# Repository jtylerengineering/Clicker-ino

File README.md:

# Clicker-ino (WIP)
A simple(ish) 433 mhz RF transceiver that uses an Arduino Uno R3 and an LCD Shield to display morse code inputs as  English.

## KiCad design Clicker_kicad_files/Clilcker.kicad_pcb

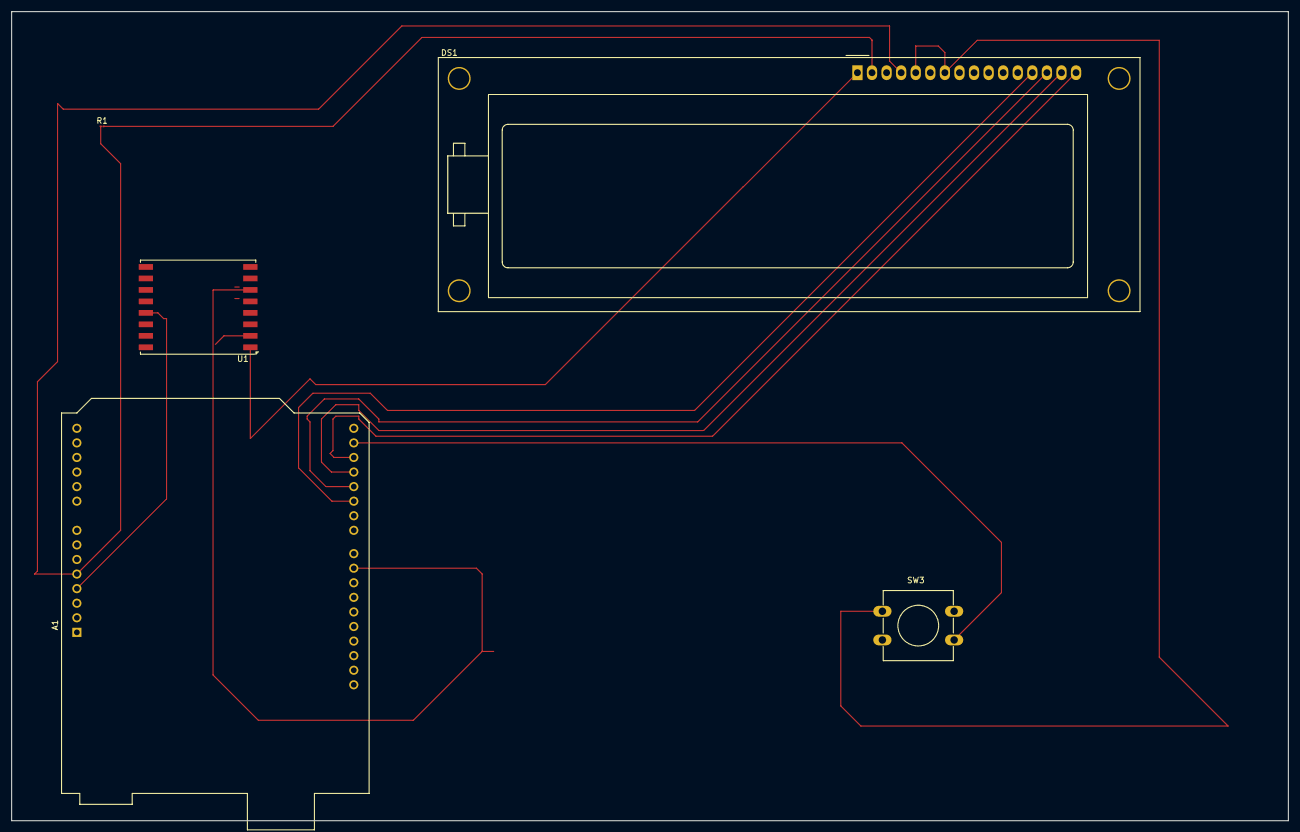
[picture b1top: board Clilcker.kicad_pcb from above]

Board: 2 copper layers, 222.5 x 141.0 mm, 5 parts (0 on the bottom side), 14 nets.

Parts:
A1: Arduino_UNO_R3
DS1: HY1602E
R1: 220 ohm; R_01005_0402Metric
SW3: SW_Push; SW_PUSH-12mm
U1: RFM69HCW; HOPERF_RFM69HW

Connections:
+5V: A1.5 (+5V), DS1.4 (VDD), R1.1
GND: A1.29 (GND), DS1.1 (LEDK), DS1.3 (VSS), DS1.5 (Vo), DS1.7 (R/~W), SW3.1, U1.1 (GND)
unnamed: A1.4 (3V3), U1.13 (3.3V)
unnamed: A1.16 (D1/TX), SW3.2
unnamed: A1.17 (D2), DS1.16 (DB7)
unnamed: A1.18 (D3), DS1.15 (DB6)
unnamed: A1.19 (D4), DS1.14 (DB5)
unnamed: A1.20 (D5), DS1.13 (DB4)
unnamed: A1.24 (D9), U1.6 (RESET)
unnamed: A1.25 (D10), U1.5 (NSS)
unnamed: A1.26 (D11), U1.3 (MOSI)
unnamed: A1.27 (D12), U1.2 (MISO)
unnamed: A1.28 (D13), U1.4 (SCK)
unnamed: DS1.2 (LEDA), R1.2
